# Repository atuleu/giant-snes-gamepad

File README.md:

# giant-snes-gamepad #

This project aims to build a Giant Super Nintendo Gamepad USB
gamepad. This repository will aim to host all instructions and how to
build and use it, as well as source code.

The idea is to construct a foot step platform were two people have to
play cooperatively on one gamepad.

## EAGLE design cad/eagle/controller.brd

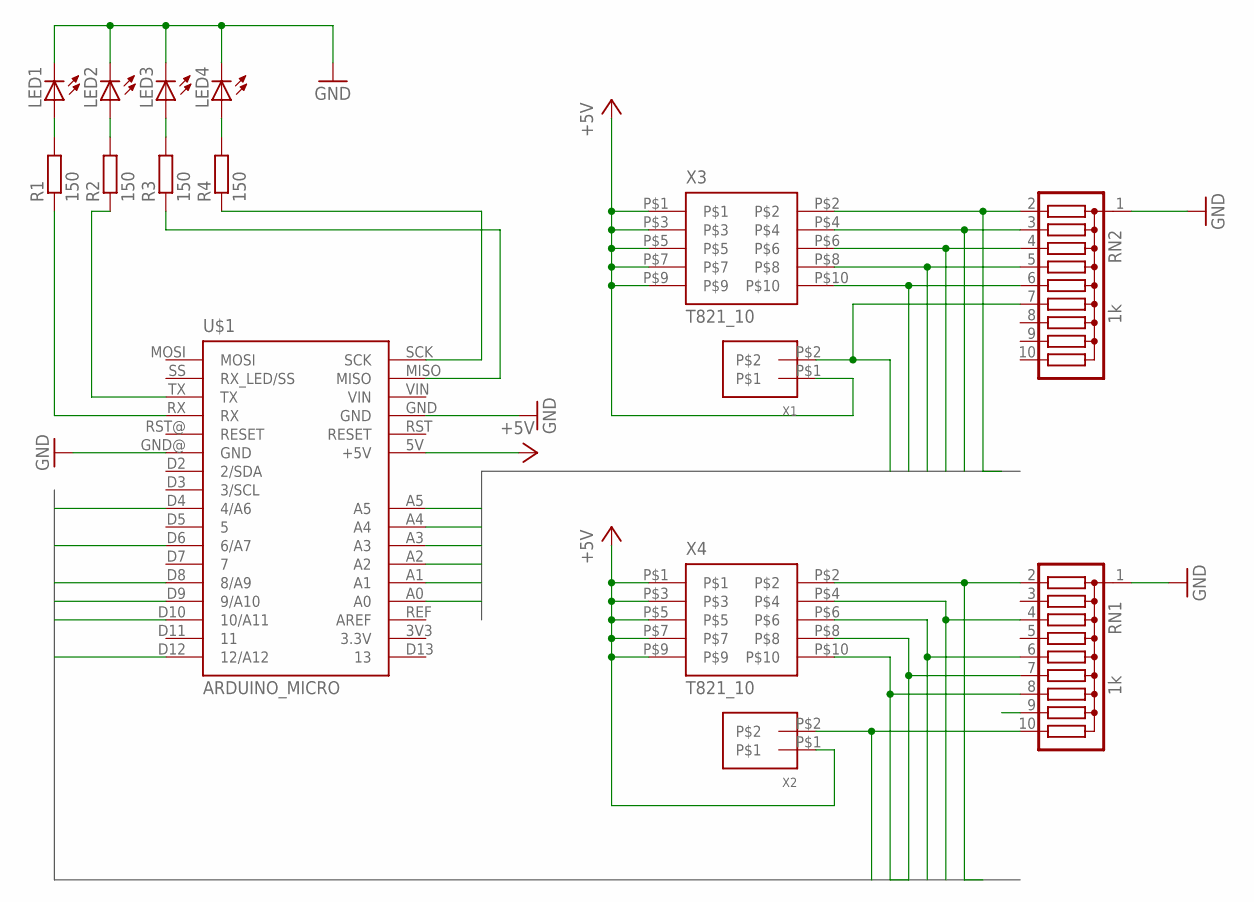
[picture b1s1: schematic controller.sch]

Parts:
LED1, LED2, LED3, LED4: LED5MM
R1, R2, R3, R4: 150; 0204/7
RN1, RN2: 1k; SIL10
U$1: ARDUINO_MICRO
X1, X2: 100MIL_2POS
X3, X4: T821_10

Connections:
+5V: U$1.5V (+5V), X1.P$1, X2.P$1, X3.P$1, X3.P$3, X3.P$5, X3.P$7, X3.P$9, X4.P$1, X4.P$3, X4.P$5, X4.P$7, X4.P$9
B0: RN2.2, U$1.A0, X3.P$2
B1: RN2.3, U$1.A1, X3.P$4
B2: RN2.4, U$1.A2, X3.P$6
B3: RN2.5, U$1.A3, X3.P$8
B4: RN2.6, U$1.A4, X3.P$10
B5: RN2.7, U$1.A5, X1.P$2
B6: RN1.2, U$1.D4 (4/A6), X4.P$2
B7: RN1.4, U$1.D6 (6/A7), X4.P$4
B8: RN1.6, U$1.D8 (8/A9), X4.P$6
B9: RN1.7, U$1.D9 (9/A10), X4.P$8
B10: RN1.8, U$1.D10 (10/A11), X4.P$10
B11: RN1.10, U$1.D12 (12/A12), X2.P$2
GND: LED1.K (C), LED2.K (C), LED3.K (C), LED4.K (C), RN1.1, RN2.1, U$1.GND, U$1.GND@ (GND)
unnamed: LED1.A, R1.2
unnamed: LED2.A, R2.2
unnamed: LED3.A, R3.2
unnamed: LED4.A, R4.2
unnamed: R1.1, U$1.RX
unnamed: R2.1, U$1.TX
unnamed: R4.1, U$1.SCK
unnamed: R3.1, U$1.MISO

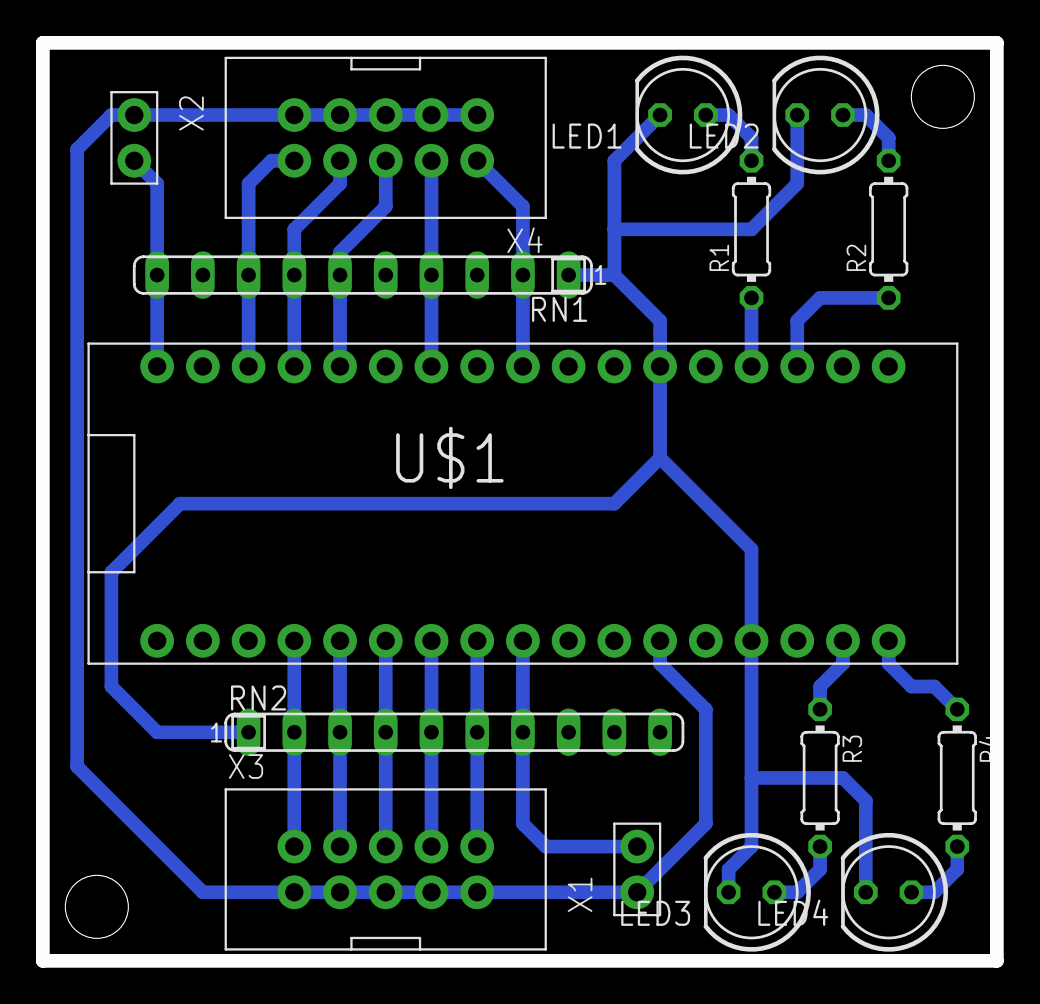
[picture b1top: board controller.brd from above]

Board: 2 copper layers, 53.0 x 51.0 mm, 15 parts (0 on the bottom side), 22 nets.

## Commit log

2013-11-08 Updates the README
2013-11-09 Adds arduino-cmake submodule
2013-11-24 Adds cmake skeleton
2013-11-24 Adds git checkout of external projects
2013-12-01 Removes the main
2013-12-01 Updates to use my head of arduino cmake
2013-12-01 Updates to head of atuleu/arduino-cmake
2013-12-01 LUFAs skeleton for a HID device
2013-12-02 Points to atuleu's fork arduino-cmake
2013-12-02 Reconfigures device to use bulk endpoint
2013-12-03 Sets a basic timer loop
2013-12-03 Makes a pure avr 4 bit clock program without _delay_ms()
2013-12-03 Squashes all application logic in its modules
2013-12-03 Makes USB Function name conventional
2013-12-03 Tries a simple HID report
2013-12-05 Makes the USB device beeing recognized on OS X and linux
2013-12-05 Adds back bulk control endpoint
    They will be usefull for device calibration. Solves also a problem
    where device was not automatically detected, due to a lack of wakeup
    instructions.
2013-12-05 Adds two input buttons
2013-12-10 Go skeleton for drivers
2013-12-11 Adds listing and opening of usb device
2013-12-12 [WIP] Adding protocol in common header
2013-12-12 Puts all communication related definition in a separate header file
2013-12-13 Made first sketch under FreeCAD
2013-12-14 Switches to C++
    Go need a go.usb
2013-12-14 First skeleton to have a nice Application wrapper
2013-12-14 Adds Gamepad class for Gamepad abstraction
2013-12-14 Adds common System error class (imported from biorob-cpp
2013-12-14 Replaces output to stderr by logging
2013-12-14 Puts library RAII wrapper
2013-12-14 Disable ncurses and debug output to stderr
2013-12-14 Implements Gamepad Listing and IF checking
2013-12-14 Makes Darwin workaround platform specific
    Due to this upstream bug ( http://www.libusb.org/ticket/171 )
    libusb_get_active_config_descriptor() segfault if the device is not
    libusb_open before. This patch address this issue for OS X only, and
    let the device in a closed state after construction (like other
    platforms).
2013-12-14 Implements Communication interface
2013-12-14 Try to fetch some data from the device
2013-12-15 Adds claiming of the interface
2013-12-15 Reports when a non-trivial packet is received
2013-12-15 Solves a bug were data transfer was not correctly handled
2013-12-15 Changes EP Addresses to match one of LUFA's
2013-12-20 Strips all bulk interface away
2013-12-21 Updates the communication protocol
2013-12-21 Recompiles with joystick interface only
2013-12-21 Makes communication over control EP
2013-12-21 Implements Gamepad::ReadAllParams() for device
2013-12-21 Adds offset to EEPROM addresses
2013-12-22 Makes reading of parameters private and automatic
2013-12-22 Implements host side communication all thread safe
2013-12-25 First skeleton of teh interface
2013-12-25 Adds CellViewer basic initialization
2013-12-25 Fixes some smalle bugs
2013-12-25 Fixes various communication bugs
2013-12-25 Makes cell value oscillating for debugging
2013-12-27 Sets default parameter values
2014-01-12 Added Base dimensions
2014-01-12 Fixup
2014-01-13 First model done
2014-01-20 Adds some notes about ADC
2014-01-24 Sets a 12 channel ADC
2014-02-22 Separated in two sub-assembly
2014-02-22 Transfers cut out on Base_Left
2014-02-22 Adds a Cart to hold gamepad
2014-02-22 Adds a cart documentation
2014-02-27 remade the mapping
2014-02-27 Adds a Save in EEPROM button
2014-02-27 Adds a timer for scanning devices
2014-03-03 Adds LEDs display
2014-03-03 Sets the internal serial number
2014-03-03 Insures devices always keep same address
2014-03-03 Implements scanning
2014-03-03 Adds device error reporting through LEDs;
2014-03-03 Report the press count
2014-03-03 Read the press count
2014-03-03 Correct reading of value
2014-03-03 Corrects the report of count number
2014-03-03 Corrects the report of cell count.
2014-03-03 Remaps the pin
2014-03-06 Corrects a count read out bug
2014-03-06 Adds schematics and PCB for the controller board
2014-03-06 new version *
